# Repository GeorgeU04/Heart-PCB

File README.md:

# Heart PCB
A simple PCB designed for my girlfriend. 
## Utilizes:
1. Circuit/Hardware Design
2. Low-Level Embedded C Programming
3. Hardware Interrupts
4. PCB Design Software (KiCad)

## Schematic

## PCB

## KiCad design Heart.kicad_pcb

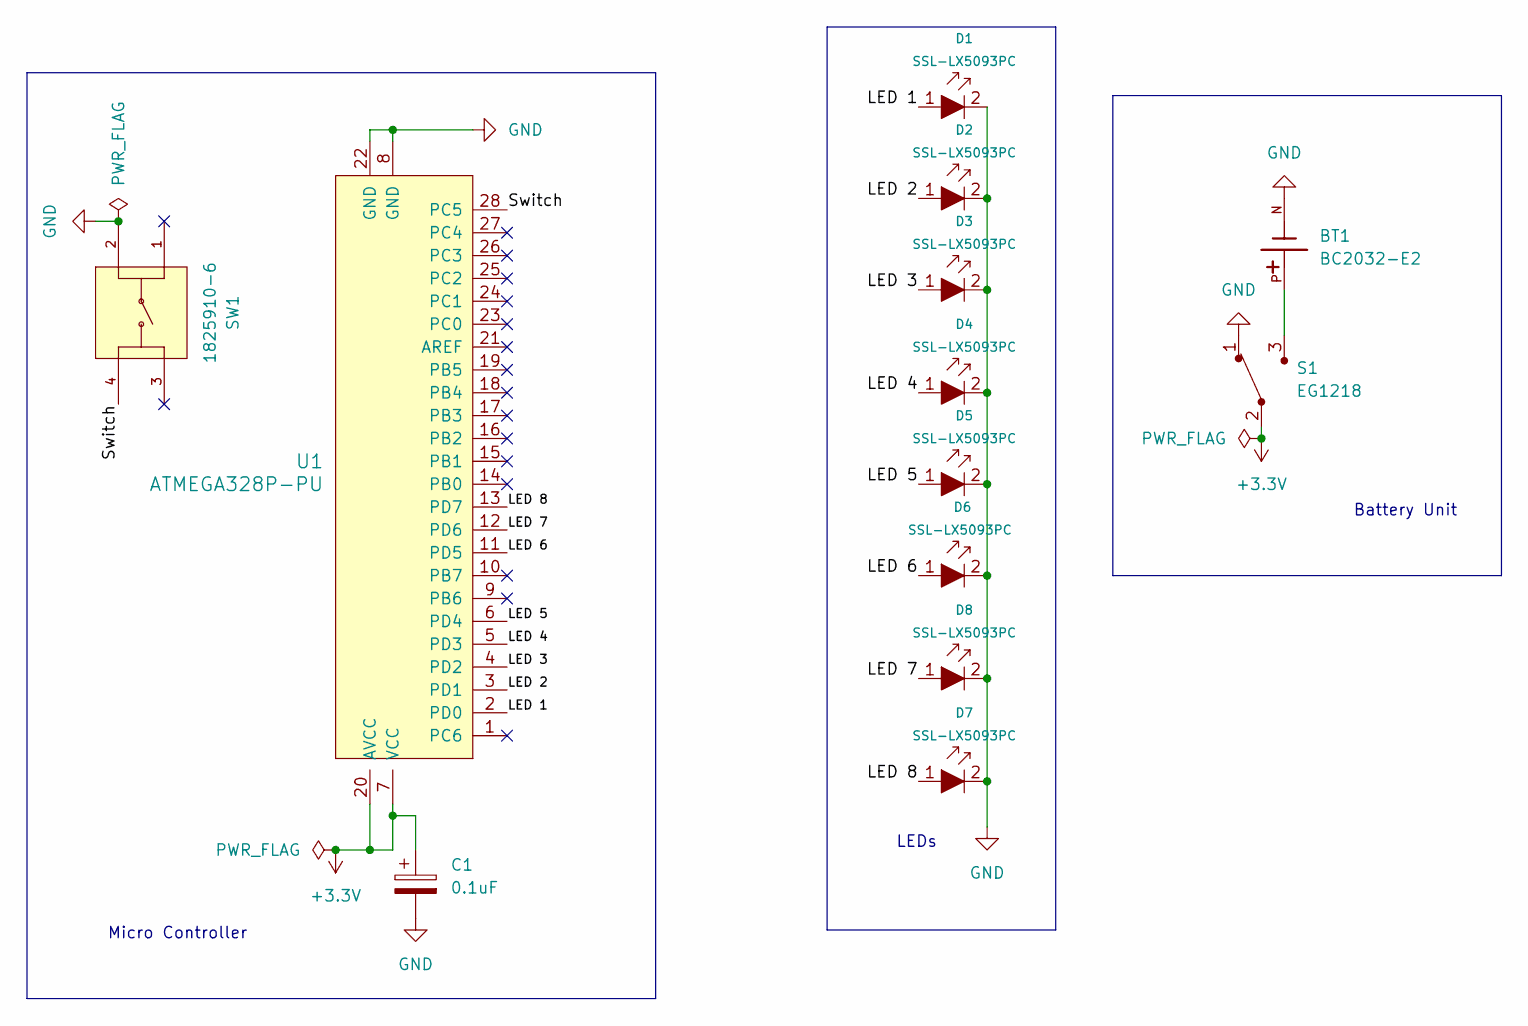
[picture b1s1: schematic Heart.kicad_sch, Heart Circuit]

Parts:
BT1: BC2032-E2; MPD_BC2032-E2; PARTREV D
C1: 0.1uF; CP_Radial_D5.0mm_P2.50mm
D1, D2, D3, D4, D5, D6, D7, D8: SSL-LX5093PC; LED_5mm_Radial; MPN SSL-LX5093PC; Digi-Key_PN 67-2062-ND
S1: EG1218; Switch_Slide_11.6x4mm_EG1218; MPN EG1218; Digi-Key_PN EG1903-ND
SW1: 1825910-6; SW_1825910-6-4; PARTREV C10
U1: ATMEGA328P-PU; DIP-28_W7.62mm; MPN ATMEGA328P-PU; Digi-Key_PN ATMEGA328P-PU-ND

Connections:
+3.3V: C1.1, S1.2, U1.7 (VCC), U1.20 (AVCC)
/LED 1: D1.1, U1.2 (PD0)
/LED 2: D2.1, U1.3 (PD1)
/LED 3: D3.1, U1.4 (PD2)
/LED 4: D4.1, U1.5 (PD3)
/LED 5: D5.1, U1.6 (PD4)
/LED 6: D6.1, U1.11 (PD5)
/LED 7: D8.1, U1.12 (PD6)
/LED 8: D7.1, U1.13 (PD7)
/Switch: SW1.4, U1.28 (PC5)
GND: BT1.N, C1.2, D1.2, D2.2, D3.2, D4.2, D5.2, D6.2, D7.2, D8.2, S1.1, SW1.2, U1.8 (GND), U1.22 (GND)
unnamed: BT1.P, S1.3

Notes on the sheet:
LEDs
Battery Unit
Micro Controller

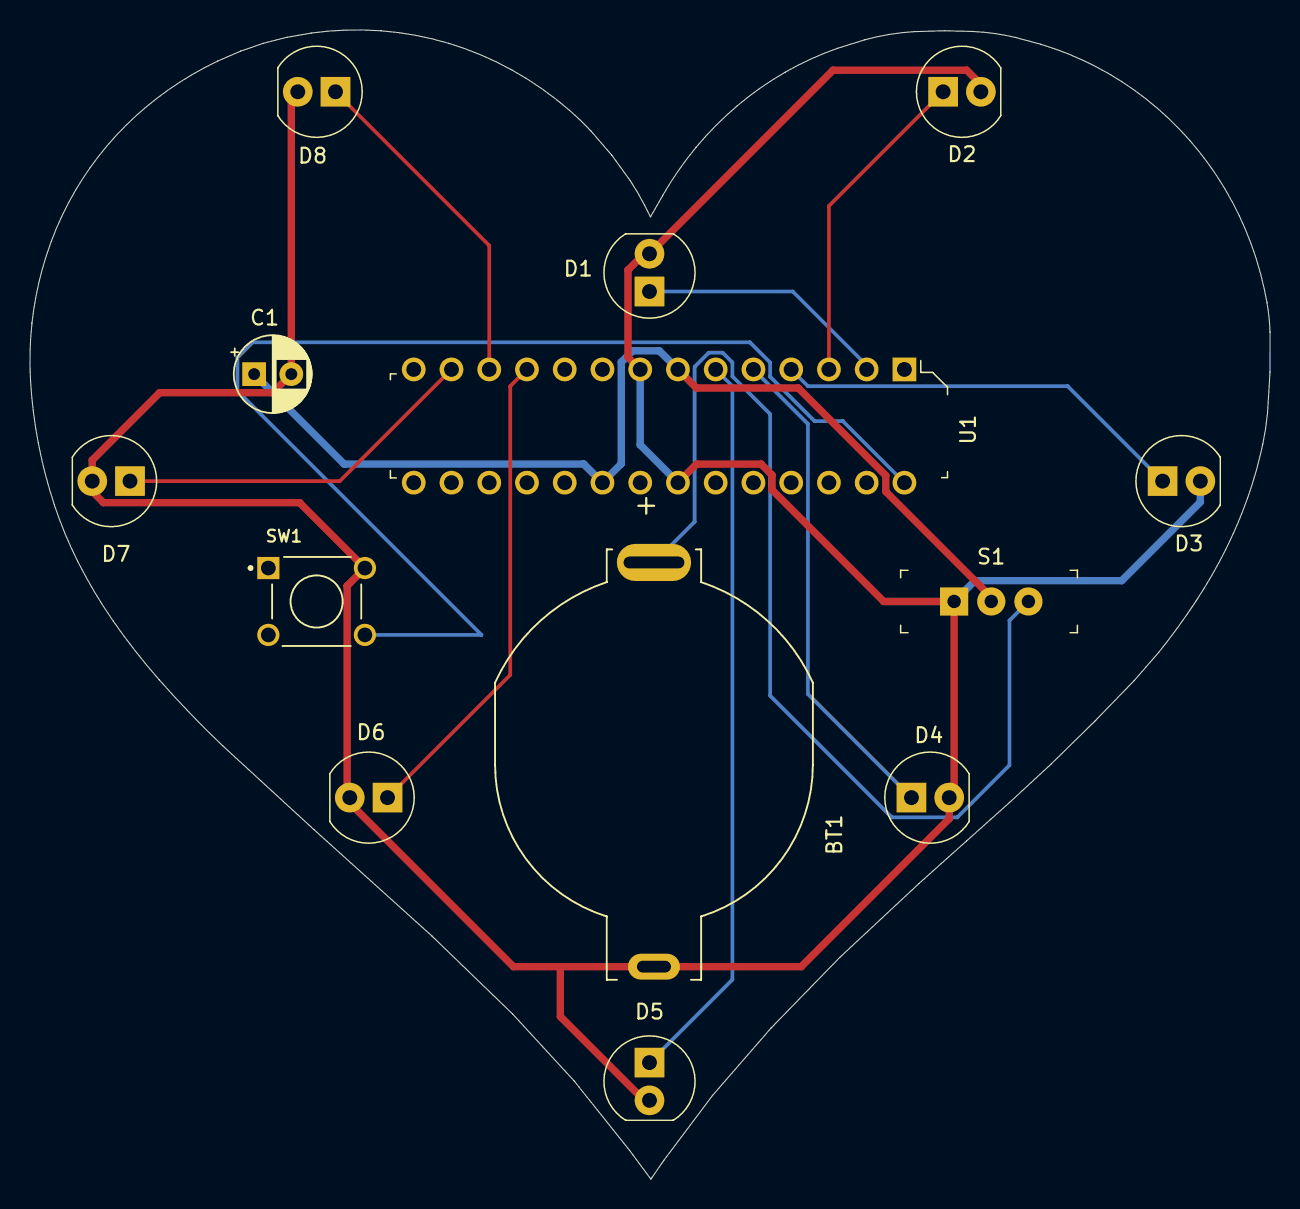
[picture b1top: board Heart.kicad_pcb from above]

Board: 2 copper layers, 83.4 x 77.3 mm, 13 parts (0 on the bottom side), 12 nets.

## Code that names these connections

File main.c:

#ifndef F_CPU					
#define F_CPU 1000000UL			// define it now as 1 MHz unsigned long
#endif

#include <avr/io.h>				
#include <util/delay.h>		
#include <avr/interrupt.h>

#define BIT_IS_SET(byte, bit) (byte & (1 << bit))
#define BIT_IS_CLEAR(byte, bit) (!(byte & (1 << bit)))

volatile uint8_t button_pressed;

int main(void) {
	button_pressed = 0;
	PCICR = (1 << PCIE1);     // Enable pin change interrupt for PCINT14 to PCINT8
    PCMSK1 = (1 << PCINT13);  // Enable PCINT13 interrupt
	
	sei();				


	DDRC &= ~(1 << PC5);	// set PC5 for input
	DDRD = 0xFF;			// all pin d set for output
	PORTC |= (1 << PC5);		// set PC5 internal pull-up resistor
    while (1) {
		if(button_pressed){
			PORTD^=(1 << PD1) | (1 << PD3) | (1 << PD5) | (1 << PD7);
			_delay_ms(250);
			PORTD^=(1 << PD0) | (1 << PD2) | (1 << PD4) | (1 << PD6);
			}
		else{
			PORTD = 0xFF;
		}
	}
	return(0);					
}

ISR(PCINT1_vect) {
	_delay_ms(40);
	if(BIT_IS_CLEAR(PINC, PC5)) {			// if switch is pressed
		button_pressed = !button_pressed;
	}
		else{}
}
